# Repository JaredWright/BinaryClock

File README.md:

# Binary Wall Clock Art Project

Source code and PCB design for a wall-mounted LED binary wall clock.

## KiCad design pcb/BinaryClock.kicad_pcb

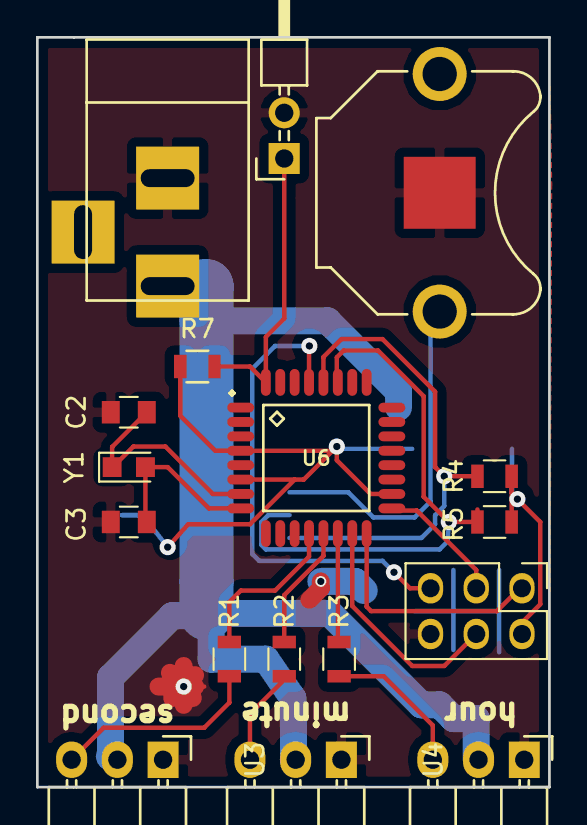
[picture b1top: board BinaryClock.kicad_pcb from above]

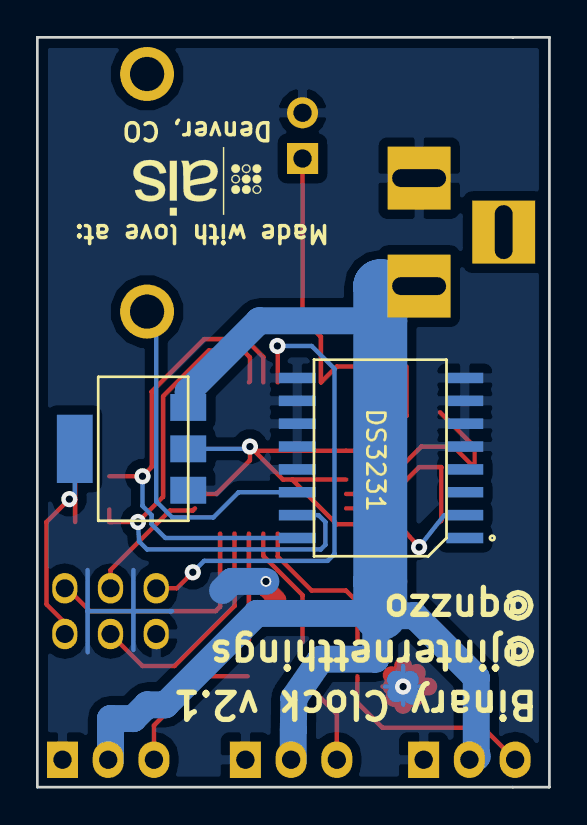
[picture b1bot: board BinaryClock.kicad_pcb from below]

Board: 2 copper layers, 28.4 x 41.7 mm, 17 parts (2 on the bottom side), 18 nets.

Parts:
BT1: Battery_Cell; Keystone_3001_1x12mm-CoinCell
C2, C3: 10pF; C_0805
CON1: AVR-ISP-6; Pin_Header_Straight_2x03_Pitch2.54mm
CON2: BARREL_JACK
R1, R2, R3: 220; R_0805
R4, R5: 1k; R_0805
R7: 10k; R_0805
U1: MC33269; SOT223_318H
U2: DS3231
U3, U4: clock_header; Pin_Header_Angled_1x03
U6: ATMEGA328-AU; QFP80P900X900X120-32
Y1: 16MHz; Crystal_SMD_2012-2pin_2.0x1.2mm_HandSoldering

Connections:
/LED1: R1.1, U3.3
/LED2: R2.1, U4.3
/MISO: CON1.1, U6.16
/MOSI: CON1.4, U6.15
/RESET: CON1.5, U6.29
/SCK: CON1.3, U6.17
/VIN: CON2.1, U1.3, U3.2, U4.2
GND: BT1.2, C2.1, C3.1, CON1.6, CON2.2, U1.1, U2.5, U2.6, U2.7, U2.8, U2.9, U2.10, U2.11, U2.12, U2.13, U3.1, U4.1, U6.3, U6.5, U6.21
unnamed: BT1.1, U2.14
unnamed: C2.2, U6.7, Y1.1
unnamed: C3.2, U6.8, Y1.2
unnamed: R1.2, U6.12
unnamed: R2.2, U6.13
unnamed: R3.2, U6.14
unnamed: R7.2, U6.32
SCL: R4.2, U2.16, U6.28
SDA: R5.2, U2.15, U6.27
VCC: CON1.2, R4.1, R5.1, R7.1, U1.2, U2.2, U6.4, U6.6, U6.18

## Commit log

2016-03-28 Initial commit for binary clock v1.0
2016-12-08 Changed colors for clock faces
2016-12-09 Removed arduino prototype from revision 1.1
2016-12-09 Added a template Vagrant file with minimal settings to build this project with VirtualBox
2016-12-09 Added initial .gitignore for build artifacts, etc
2016-12-09 Added led blink test program/Makefile to test build toolchain and vagrant environment
2016-12-16 Skeleton code for reading/writing from the DS3231 real-time clock. Does not work yet
2016-12-16 Skeleton code for read/writing from the TWI interface on an ATMEGA328P. Does not work yet
2016-12-16 Driver for WS2812b LED lights (neopixels) on a 20Mhz AVR
2016-12-16 Helper functions for controlling strands of LEDs using the WS2812b driver
2016-12-16 Test application for WS2812B driver and led helper functions. Currently, hardcoded to output on PORTB, Pin 0
2016-12-17 Makefile cleanup
2016-12-17 More makefile cleanup
2016-12-17 Fixes for compilation errors, i2c functions still incomplete
2016-12-17 i2c driver refactored
2016-12-17 Changed ds3231 driver to use modifications from last commit
2017-01-22 Working I2C ds3231 driver, tested on ATMEGA328P
2017-01-25 Initial commit for the PCB schematic
2017-02-06 refactored clock helper functions
2017-02-06 Moved comments from .c to .h for ds3231 helper functions
2017-02-06 Moved comments from .c to .h for i2c functions
2017-02-06 Updated led and ws2812b driver to allow for initializtion on any port/pin, instead of a hard coded port and pin
2017-02-06 Added teensy loader programmer support to makefile, moved app initialization code from clock.c to main.c
2017-02-06 Moved configurable clock paramters (colors, etc) to clock.h
2017-02-06 Moved source code files to src/ and header files for inc/
2017-02-22 pcb layout begun
2017-02-25 Progress toward high level board layout. Board is still missing a voltage reulator
2017-02-25 Added some external footprint libraries for the DS3231 RTC and CoinCell battery holders
2017-02-25 Renamed project in README
2017-03-01 Added voltage regulator to pcb schematic and layout. Started routing on the board layout
2017-03-08 Finished initial attempt at routing
2017-03-10 Ground planes added
2017-04-01 Moved left edge of the board layout to increase surface area for the ground plane
2017-04-01 Updated gitignore to exclude build artifacts
2017-04-01 Added silkscreen text
2017-05-27 Added schematic connections for an external led on/off switch
2017-05-27 Changed atmega328 schematic part to be used from a different kicad library
2017-05-27 Removed old bogus atmega328 footprint, replaced with correct TQFP32
2017-05-27 Re-routing with new atmega footprint
2017-05-27 Added on-board pullup resistor for external on/off switch
2017-08-16 Updated via sizes to increase annular rings
2017-08-16 Hack to connect vias to ground plane.
2017-09-21 Added a small support program to intialize the clock's time
